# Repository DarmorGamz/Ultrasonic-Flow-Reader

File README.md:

<!-- PROJECT LOGO -->
<br />
<div align="center">
  
<h3 align="center">Ultrasonic Flow Reader</h3>

  <p align="center">
    The Ultra Sonic Flow Reader is a non-invasive, innovative solution that enables real-time water flow monitoring in pipes using ultrasonic waves. Designed for homeowners, residential and industrial building owners, and property managers, this device helps reduce installation costs and risks associated with traditional inline installations, while promoting water conservation and potential cost savings.
    <br />
    <br />
    <a href="https://github.com/DarmorGamz/Ultrasonic-Flow-Reader">View Demo</a>
    ·
    <a href="https://github.com/DarmorGamz/Ultrasonic-Flow-Reader/issues">Report Bug</a>
    ·
    <a href="https://github.com/DarmorGamz/Ultrasonic-Flow-Reader/issues">Request Feature</a>
  </p>
</div>

### Built With

[![C][C.com]][C-url]

[![HTML.com]][HTML-url] [![CSS3.com]][CSS3-url] [![JavaScript.com]][JavaScript-url]

[![PHP.com]][PHP-url] [![MYSQL.com]][MYSQL-url] [![Linux.com]][Linux-url] [![AWS.com]][AWS-url]

<!-- ABSTRACT -->
## ABSTRACT
The Ultra Sonic Flow Reader is a non-invasive solution designed to measure the flow of water in pipes using ultrasonic waves, eliminating the need for costly and time-consuming inline installation by licensed plumbers. Targeting homeowners, residential and industrial building owners, and property managers, this innovative device empowers users to monitor their water usage in real time, leading to potential cost savings and improved water conservation. The project employs ultrasonic transducers, a SAMD20 microcontroller, Winc1500 for WiFi, ENC28J60 for Ethernet, and leverages AWS for RDS, EC2, and Route53. The firmware is developed using Embedded C, with a PHP backend, and a frontend designed using HTML, CSS, and JavaScript. The Ultra Sonic Flow Reader is expected to minimize the need for hiring plumbers and reduce the risk of potential damage associated with traditional inline installations. The project's final demonstration is scheduled for April 13, 2023, showcasing a user-friendly and efficient solution for real-time water usage monitoring.

<!-- INTRODUCTION -->
## INTRODUCTION

#### Enhancing Water Usage Monitoring
The Ultra Sonic Flow Reader project was conceived with the primary goal of addressing a pressing need in the field of water monitoring and management. Traditional methods for measuring water flow in pipes typically require invasive installations and the assistance of licensed plumbers. This process can be both expensive and time-consuming, posing significant challenges for homeowners, residential and industrial building owners, and property managers who are looking to monitor their water usage in real time. As water scarcity becomes an increasingly critical global issue, there is a growing demand for innovative solutions that facilitate efficient water management and conservation.

#### Target Users and Applications
The project's scope encompasses the design and development of a non-invasive, cost-effective, and user-friendly device capable of real-time water usage monitoring. The Ultra Sonic Flow Reader employs advanced technologies such as ultrasonic transducers, a SAMD20 microcontroller, Winc1500 for WiFi, and ENC28J60 for Ethernet. In addition, it leverages Amazon Web Services (AWS) for database management (RDS), cloud computing (EC2), and domain name management (Route53). The device's firmware is developed using Embedded C, while the backend is built using PHP, and the frontend is designed with HTML, CSS, and JavaScript.

#### Project Development Phases
The approach taken to the project involved extensive research, planning, and execution of various design phases, including hardware and software development, integration, and testing. The interdisciplinary team, consisting of Darren Morrison, Austin Cormier, and Carter Glynn, collaborated closely under the supervision of Professors Hameed Al-Aubodah, Hamood-ur Rehman, Jane Carr, and Mehrdad Hajivandi to bring the project to fruition.

#### Challenges of Traditional Inline Installations
The Ultra Sonic Flow Reader project has been designed with a focus on simplicity, adaptability, and ease of use. Recognizing the diverse needs of homeowners, property managers, and residential and industrial building owners, the team has strived to create a solution that caters to a wide range of applications. The device's non-invasive nature ensures that it can be installed without causing disruptions to existing infrastructure or requiring specialized skills.
Throughout the project, the team has been guided by a set of core principles, including innovation, collaboration, and a commitment to addressing real-world challenges. These principles have driven the development process and informed key decisions, such as the selection of appropriate hardware components, software design, and integration strategies. Additionally, the team has placed a strong emphasis on testing and validation, ensuring that the Ultra Sonic Flow Reader consistently delivers accurate and reliable results.
As the project progresses towards its final demonstration, scheduled for April 13, 2023, the team remains dedicated to refining the Ultra Sonic Flow Reader and addressing any outstanding issues or limitations. The team acknowledges that further research and development efforts will be essential in enhancing the device's applicability to a wider range of pipe sizes and optimizing its power supply requirements. By addressing these challenges, the Ultra Sonic Flow Reader will be better positioned to meet the needs of its target users and make a positive impact on water management and conservation efforts.
In summary, the Ultra Sonic Flow Reader project represents a significant advancement in the field of water monitoring and management. By offering a non-invasive, cost-effective, and user-friendly solution for real-time water usage monitoring, the device has the potential to transform the way homeowners, building owners, and property managers approach water conservation. This report serves to document the project's journey from conception to completion, providing a comprehensive account of the team's research, development, and validation efforts.
This report details the problem statement, which outlines the challenges faced by traditional inline water flow monitoring systems and the need for a non-invasive alternative. The development process, including the project proposal, changes and decisions made throughout the project, and challenges encountered in implementation, is thoroughly discussed. Furthermore, the report presents the testing procedures and results, including Sprint tests, Product Validation tests, and an assessment of whether all user needs and requirements have been met. To support the report, relevant research materials, schematics, flowcharts, source code, and other documentation are included in the appendices.

#### Problem Statement
The Ultra Sonic Flow Reader project aims to revolutionize water monitoring by providing a solution that eliminates the need for hiring plumbers and reduces the risk of potential damage associated with traditional inline installations. By offering real-time water usage monitoring, the device empowers users to make informed decisions about their water consumption, leading to potential cost savings and improved water conservation efforts.

#### Report Structure
This report is organized into several sections, each focusing on a different aspect of the project. Following the introduction, the report details the problem statement, project development process, testing procedures and results, and any remaining limitations or challenges. The appendices provide additional documentation and materials to support the main body of the report.

<!-- INTRODUCTION -->
## DISCUSSION
The development of the Ultra Sonic Flow Reader project can be broken down into several key phases, each contributing to the overall success of the project. In this section, we discuss the progression of the project from proposal to completion, highlighting the changes and decisions made, challenges faced during implementation, and the various tests conducted.

#### Project Proposal and Initial Development
The project proposal was the foundation for the Ultra Sonic Flow Reader, outlining the primary objectives, expected outcomes, and proposed timeline. The team performed extensive research on existing flow measurement methods, identifying the limitations and drawbacks of traditional inline installations. This analysis informed the decision to pursue a non-invasive solution using ultrasonic waves for flow measurement.
Initial development focused on selecting appropriate hardware components, such as the ultrasonic transducers and SAMD20 microcontroller, and designing the basic hardware structure. The team also began work on the firmware using Embedded C and the backend using PHP, laying the groundwork for further development.

#### Iterative Development and Integration
Throughout the project, the team adopted an iterative development process, allowing for continuous improvements and adjustments. Hardware and software components were developed in parallel, with regular integration and testing to ensure compatibility and functionality.
Several changes were made during the development process, including the addition of Winc1500 for WiFi connectivity, ENC28J60 for Ethernet support, and the utilization of AWS for cloud-based services. These changes were made to enhance the device's usability and align it with modern IoT-based solutions.

#### Challenges and Implementation
The team encountered various challenges during the implementation phase. These included limited funding, time constraints, and complexities in debugging and hardware design. To overcome these challenges, the team members worked collaboratively, leveraging their individual skills and expertise to find solutions.
One of the key challenges was ensuring accurate flow measurement across various pipe sizes and materials. The team focused on refining the ultrasonic transducer placement and signal processing algorithms to achieve reliable results. Furthermore, optimizing power consumption was a priority, and the team worked on designing an energy-efficient system that minimizes the need for additional power sources.

#### Testing and Results
The Ultra Sonic Flow Reader underwent a series of tests to ensure its functionality, accuracy, and reliability. These tests included User Information Handling, API testing, Hardware Event Handling, and Hardware Timers testing. Each test was designed to evaluate specific aspects of the device's performance and identify areas for improvement.
The results of these tests showed that the Ultra Sonic Flow Reader met most user needs and requirements, delivering accurate flow measurements and a responsive user interface. However, some limitations were identified, such as the need for a more modular sensor PCB mount and optimization of the power supply.

#### References to Appendices
Throughout the report, references are made to the appendices, which contain supplementary material such as research materials, schematics, flowcharts, and source code. These documents provide a more in-depth understanding of the Ultra Sonic Flow Reader's design and development process and can be used to replicate the project and verify its results.

<!-- RECOMMENDATION -->
## RECOMMENDATION
Based on the findings and conclusions of the Ultra Sonic Flow Reader project, the following recommendations are provided to guide future research, development, and commercialization efforts.

#### Wider Pipe Size Compatibility
The current design supports only 1-inch pipes, limiting the applicability of the device. Future research should focus on developing a more modular sensor PCB mount, enabling compatibility with a broader range of pipe sizes to cater to various residential and industrial applications.

#### Power Supply Optimization
The power supply requirements of the current design demand a minimum of 12V for the sensor PCB to function. Optimizing the power supply to support lower voltage levels could enhance the device's energy efficiency, minimize the need for additional power sources, and potentially extend its battery life.

#### Enhanced User Interface
While the existing user interface is functional, it could benefit from further refinement to improve user experience. Future iterations should consider incorporating more advanced data visualization features, customizable alerts, and a mobile application for increased accessibility.

#### Market Research and Consumer Feedback
Conduct market research and solicit feedback from potential end-users to gain insights into user needs, preferences, and potential use cases. This information can inform future design decisions and contribute to the development of a more market-ready product.

#### Compliance with Regulatory Standards
As the project moves towards commercialization, it is crucial to research safety requirements, electronic stamping, and other relevant industry standards to ensure the Ultra Sonic Flow Reader complies with all necessary regulations.

#### Cost Reduction and Production Efficiency
To improve profit margins and streamline production, consider bulk purchasing of components, outsourcing board soldering, and adopting lean manufacturing practices.

#### Long-term Testing and Reliability
Further long-term testing should be conducted to assess the device's durability, performance consistency, and overall reliability under various environmental conditions and extended usage periods.
By addressing these recommendations, the Ultra Sonic Flow Reader can evolve into a more refined and market-ready product, better positioned to meet the needs of its target users and contribute significantly to water conservation efforts.

<!-- APPENDICES -->
## APPENDICES
#### Schematics

Fig. 1.	MCU - Atmel SAMD20 circuit.

Fig. 2.	Wifi – Winc1500 circuit.

Fig. 3.	Ethernet – ENC28J60 circuit.

Fig. 4.	Sensor – Ultra sonic flow reader circuit.   

#### Flowcharts

Fig. 5. Cloud – AWS design flowchart

<!-- GETTING STARTED -->
## Getting Started

This is an example of how you may give instructions on setting up your project locally.
To get a local copy up and running follow these simple example steps.

### Prerequisites

### Installation

<p align="right">(<a href="#readme-top">back to top</a>)</p>

<!-- CONTRIBUTING -->
## Contributing

Contributions are what make the open source community such an amazing place to learn, inspire, and create. Any contributions you make are **greatly appreciated**.

If you have a suggestion that would make this better, please fork the repo and create a pull request. You can also simply open an issue with the tag "enhancement".
Don't forget to give the project a star! Thanks again!

1. Fork the Project
2. Create your Feature Branch (`git checkout -b feature/AmazingFeature`)
3. Commit your Changes (`git commit -m 'Add some AmazingFeature'`)
4. Push to the Branch (`git push origin feature/AmazingFeature`)
5. Open a Pull Request

<p align="right">(<a href="#readme-top">back to top</a>)</p>

<!-- LICENSE -->
## License

Distributed under the Eyedro Green Solutions License. See `LICENSE.txt` for more information.

<p align="right">(<a href="#readme-top">back to top</a>)</p>

<!-- CONTACT -->
## Contact

Darren Morrison - darren09@live.ca  
Austin Cormier - austin14cormier@gmail.com   
Carter Glynn - carter.glynn14@gmail.com  

Project Link: [https://github.com/DarmorGamz/Ultrasonic-Flow-Reader](https://github.com/DarmorGamz/Ultrasonic-Flow-Reader)

<p align="right">(<a href="#readme-top">back to top</a>)</p>

<!-- ACKNOWLEDGMENTS -->
## Acknowledgments
We are deeply grateful to the following individuals for their invaluable contributions, guidance, and support during the development of the Ultra Sonic Flow Reader project:   

#### Dr. Hameed Al-Aubodah, PhD
*For his expertise in electrical theory (DC, AC, Transmission lines) and digital design, and for being an inspiring role model in the engineering field.*

#### Dr. Hamood-Ur Rehman, PhD
*For sharing essential software and programming knowledge, ensuring elegant, readable, and maintainable code, and for setting high expectations that contributed to the project's success.*

#### Dr. Mehrdad Hajivandi, PhD P.Eng
*For his guidance in mathematics and advanced thinking principles crucial to the project's development.*

#### Jane Carr
*For her expertise in testing, debugging, verification, and documentation, which played a significant role in the project's completion.*   
<br />
We also extend our appreciation to Eyedro Green Solutions for their generous funding, access to lab equipment, and invaluable mentorship throughout the project. Special thanks to:   

#### Trevor Orton, CEO
*For his guidance in cloud computing, backend development, and writing and maintaining quality code.*

#### Nick Gamble, CFO
*For sharing his expertise in embedded software, embedded systems, networking, and data analysis.*

#### Jeff Conley
*For his dedication to hardware design, product specifications, circuit design, PCB assembly, and document review.*  

<p align="right">(<a href="#readme-top">back to top</a>)</p>

<!-- REFERENCES -->
## References

T. Dean, "Sonar," Brown University, [Online]. Available: https://cs.brown.edu/people/tdean/courses/cs148/02/sonar.html.  
D. Russell, "The Doppler Effect," Kettering University, [Online]. Available: https://web.archive.org/web/20071119085900/http://www.kettering.edu/~drussell/Demos/doppler/doppler.html.  
University of Bristol, "Time-of-Flight Mass Spectrometry," [Online]. Available: https://web.archive.org/web/20120310184539/http://www.chm.bris.ac.uk/ms/theory/tof-massspec.html.  
J. Steensgaard, "Bootstrapped low-voltage analog switches," in 1999 IEEE International Symposium on Circuits and Systems (ISCAS), Orlando, FL, USA, 1999, pp. 29-32, vol.2, doi: 10.1109/ISCAS.1999.780611.  
Microchip Technology Inc., "SAMD20 Family Datasheet," [Online]. Available: https://ww1.microchip.com/downloads/en/DeviceDoc/SAM_D20_Family_Datasheet_DS60001504C.pdf.  
Microchip Technology Inc., "ENC28J60 Stand-Alone Ethernet Controller with SPI Interface," [Online]. Available: https://ww1.microchip.com/downloads/aemDocuments/documents/OTH/ProductDocuments/DataSheets/39662e.pdf. 
Microchip Technology Inc., "ATWINC15x0-MR210xB IEEE 802.11 b/g/n SmartConnect IoT Module," [Online]. Available: https://ww1.microchip.com/downloads/aemDocuments/documents/WSG/ProductDocuments/DataSheets/ATWINC15x0-MR210xB-IEEE-802.11-b-g-n-SmartConnect-IoT-Module-DS70005304E.pdf.  
Amazon Web Services, "Amazon EC2 User Guide," [Online]. Available: https://docs.aws.amazon.com/AWSEC2/latest/UserGuide/concepts.html.  
Amazon Web Services, "Amazon RDS User Guide," [Online]. Available: https://docs.aws.amazon.com/AmazonRDS/latest/UserGuide/Welcome.html.  

<p align="right">(<a href="#readme-top">back to top</a>)</p>

<!-- MARKDOWN LINKS & IMAGES -->
<!-- https://www.markdownguide.org/basic-syntax/#reference-style-links -->
[contributors-shield]: https://img.shields.io/github/contributors/DarmorGamz/Ultrasonic-Flow-Reader.svg?style=for-the-badge
[contributors-url]: https://github.com/DarmorGamz/Ultrasonic-Flow-Reader/graphs/contributors
[forks-shield]: https://img.shields.io/github/forks/DarmorGamz/Ultrasonic-Flow-Reader.svg?style=for-the-badge
[forks-url]: https://github.com/DarmorGamz/Ultrasonic-Flow-Reader/network/members
[stars-shield]: https://img.shields.io/github/stars/DarmorGamz/Ultrasonic-Flow-Reader.svg?style=for-the-badge
[stars-url]: https://github.com/DarmorGamz/Ultrasonic-Flow-Reader/stargazers
[issues-shield]: https://img.shields.io/github/issues/DarmorGamz/Ultrasonic-Flow-Reader.svg?style=for-the-badge
[issues-url]: https://github.com/DarmorGamz/Ultrasonic-Flow-Reader/issues
[license-shield]: https://img.shields.io/github/license/DarmorGamz/Ultrasonic-Flow-Reader.svg?style=for-the-badge
[license-url]: https://github.com/DarmorGamz/Ultrasonic-Flow-Reader/blob/master/LICENSE.txt
[linkedin-shield]: https://img.shields.io/badge/-LinkedIn-black.svg?style=for-the-badge&logo=linkedin&colorB=555
[linkedin-url]: https://linkedin.com/in/darren--morrison

[C.com]: https://img.shields.io/badge/c-%2300599C.svg?style=for-the-badge&logo=c&logoColor=white
[C-url]: https://www.cprogramming.com
[PHP.com]: https://img.shields.io/badge/php-%23777BB4.svg?style=for-the-badge&logo=php&logoColor=white
[PHP-url]: https://www.php.net/
[MYSQL.com]: https://img.shields.io/badge/mysql-%2300f.svg?style=for-the-badge&logo=mysql&logoColor=white
[MYSQL-url]: https://www.mysql.com/
[HTML.com]: https://img.shields.io/badge/html5-%23E34F26.svg?style=for-the-badge&logo=html5&logoColor=white
[HTML-url]: https://www.w3.org/html/#:~:text=W3C%20HTML&text=https%3A%2F%2Fhtml.spec.whatwg,is%20the%20current%20HTML%20standard.
[CSS3.com]: https://img.shields.io/badge/css3-%231572B6.svg?style=for-the-badge&logo=css3&logoColor=white
[CSS3-url]: https://www.css3.com/
[JavaScript.com]: https://img.shields.io/badge/javascript-%23323330.svg?style=for-the-badge&logo=javascript&logoColor=%23F7DF1E
[JavaScript-url]: https://www.javascript.com/

[Linux.com]: https://img.shields.io/badge/Linux-FCC624?style=for-the-badge&logo=linux&logoColor=black
[Linux-url]: https://aws.amazon.com/amazon-linux-2/

[AWS.com]: https://img.shields.io/badge/AWS-%23FF9900.svg?style=for-the-badge&logo=amazon-aws&logoColor=white
[AWS-url]: https://aws.amazon.com/

[PHPStorm.com]: https://img.shields.io/badge/phpstorm-143?style=for-the-badge&logo=phpstorm&logoColor=black&color=black&labelColor=darkorchid
[PHPStorm-url]: https://www.jetbrains.com/phpstorm/

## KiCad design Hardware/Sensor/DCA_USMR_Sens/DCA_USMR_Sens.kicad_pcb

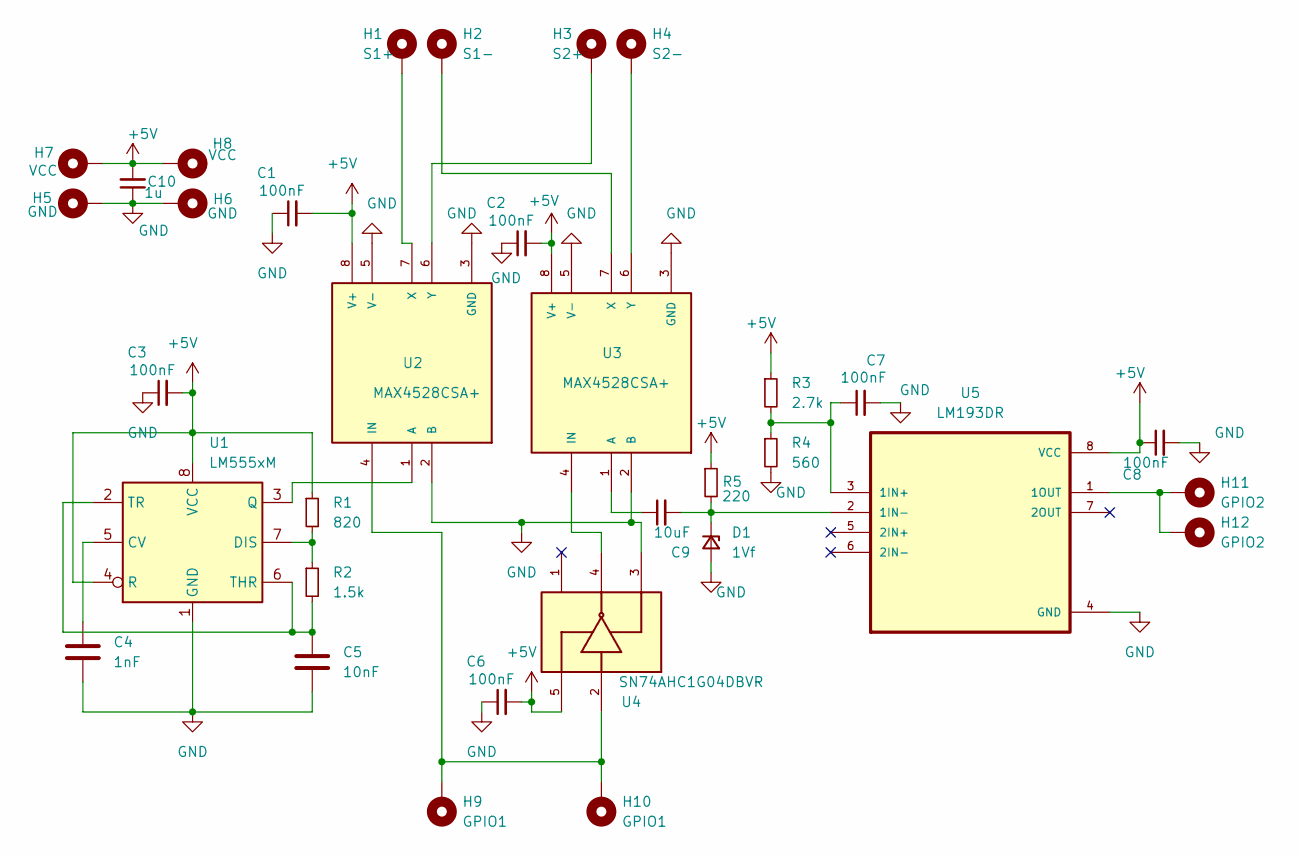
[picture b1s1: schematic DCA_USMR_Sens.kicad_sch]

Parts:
C1, C2, C3, C6, C7, C8: 100nF; C_0402_1005Metric
C4: 1nF; C_0402_1005Metric
C5: 10nF; C_0402_1005Metric
C9: 10uF; C_0402_1005Metric
C10: 1u; C_0603_1608Metric
D1: 1Vf; DIOAD835W50L444D203
H1: S1+; Pin_D0.7mm_L6.5mm_W1.8mm_FlatFork
H2: S1-; Pin_D0.7mm_L6.5mm_W1.8mm_FlatFork
H3: S2+; Pin_D0.7mm_L6.5mm_W1.8mm_FlatFork
H4: S2-; Pin_D0.7mm_L6.5mm_W1.8mm_FlatFork
H5, H6: GND; Pin_D0.7mm_L6.5mm_W1.8mm_FlatFork
H7, H8: VCC; Pin_D0.7mm_L6.5mm_W1.8mm_FlatFork
H9, H10: GPIO1; Pin_D0.7mm_L6.5mm_W1.8mm_FlatFork
H11, H12: GPIO2; Pin_D0.7mm_L6.5mm_W1.8mm_FlatFork
R1: 820; R_0402_1005Metric
R2: 1.5k; R_0402_1005Metric
R3: 2.7k; R_0402_1005Metric
R4: 560; R_0402_1005Metric
R5: 220; R_0402_1005Metric
U1: LM555xM; SOIC-8_3.9x4.9mm_P1.27mm
U2, U3: MAX4528CSA+; SOIC127P600X175-8N
U4: SN74AHC1G04DBVR; SOT95P280X145-5N; PARTREV AD
U5: LM193DR; SOIC127P599X175-8N

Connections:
+5V: C1.2, C2.2, C3.2, C6.2, C8.1, C10.2, H7.1, H8.1, R1.1, R3.1, R5.1, U1.4 (R), U1.8 (VCC), U2.8 (V+), U3.8 (V+), U4.5, U5.8 (VCC)
GND: C1.1, C2.1, C3.1, C4.2, C5.2, C6.1, C7.2, C8.2, C10.1, D1.2 (A), H5.1, H6.1, R4.2, U1.1 (GND), U2.2 (B), U2.3 (GND), U2.5 (V-), U3.2 (B), U3.3 (GND), U3.5 (V-), U4.3, U5.4 (GND)
unnamed: C4.1, U1.5 (CV)
unnamed: C5.1, R2.2, U1.2 (TR), U1.6 (THR)
unnamed: C7.1, R3.2, R4.1, U5.3 (1IN+)
unnamed: C9.1, U3.1 (A)
unnamed: C9.2, D1.1 (K), R5.2, U5.2 (1IN-)
unnamed: R1.2, R2.1, U1.7 (DIS)
unnamed: U1.3 (Q), U2.1 (A)
unnamed: H9.1, H10.1, U2.4 (IN), U4.2
unnamed: H3.1, U2.6 (Y)
unnamed: H1.1, U2.7 (X)
unnamed: U3.4 (IN), U4.4
unnamed: H4.1, U3.6 (Y)
unnamed: H2.1, U3.7 (X)
unnamed: H11.1, H12.1, U5.1 (1OUT)

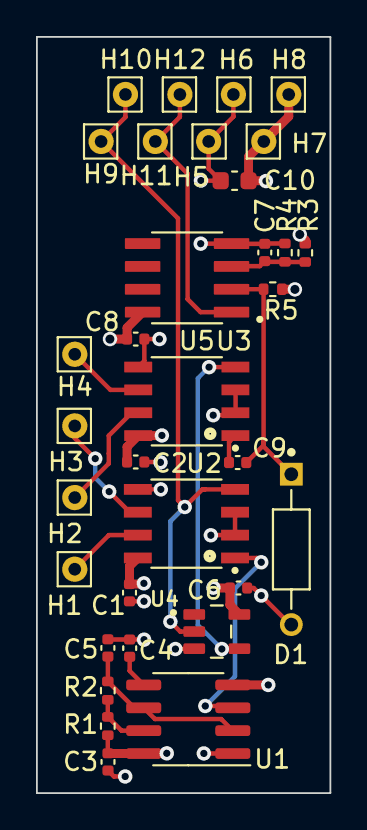
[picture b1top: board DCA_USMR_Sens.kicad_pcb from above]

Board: 4 copper layers, 16.3 x 42.0 mm, 33 parts (0 on the bottom side), 16 nets.

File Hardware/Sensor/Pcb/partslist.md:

# PARTS LIST

### IC's

**(1x)** Comparator - LM193DR <br>
https://www.digikey.ca/en/products/detail/texas-instruments/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 <br>

**(2x)** Switch - MAX4528CSA+ <br>
https://www.digikey.ca/en/products/detail/analog-devices-inc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 <br>

**(1x)** 555 Timer - LM555CMMX/NOPB  <br>
https://www.digikey.ca/en/products/detail/texas-instruments/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 <br>

**(1x)** Inverter - SN74AHC1G04DBVR <br>
https://www.digikey.ca/en/products/detail/texas-instruments/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 <br>

### CAPACITORS

**(1x)** 1uF <br>
**(6x)** 100nF <br>
**(2x)** 10nF <br>
**(1x)** 1nF <br>

### RESISTORS

**(1x)** 220Ω <br>
**(1x)** 560Ω <br>
**(1x)** 820Ω <br>
**(1x)** 1.5kΩ <br>
**(1x)** 2.7kΩ <br>

### DIODE

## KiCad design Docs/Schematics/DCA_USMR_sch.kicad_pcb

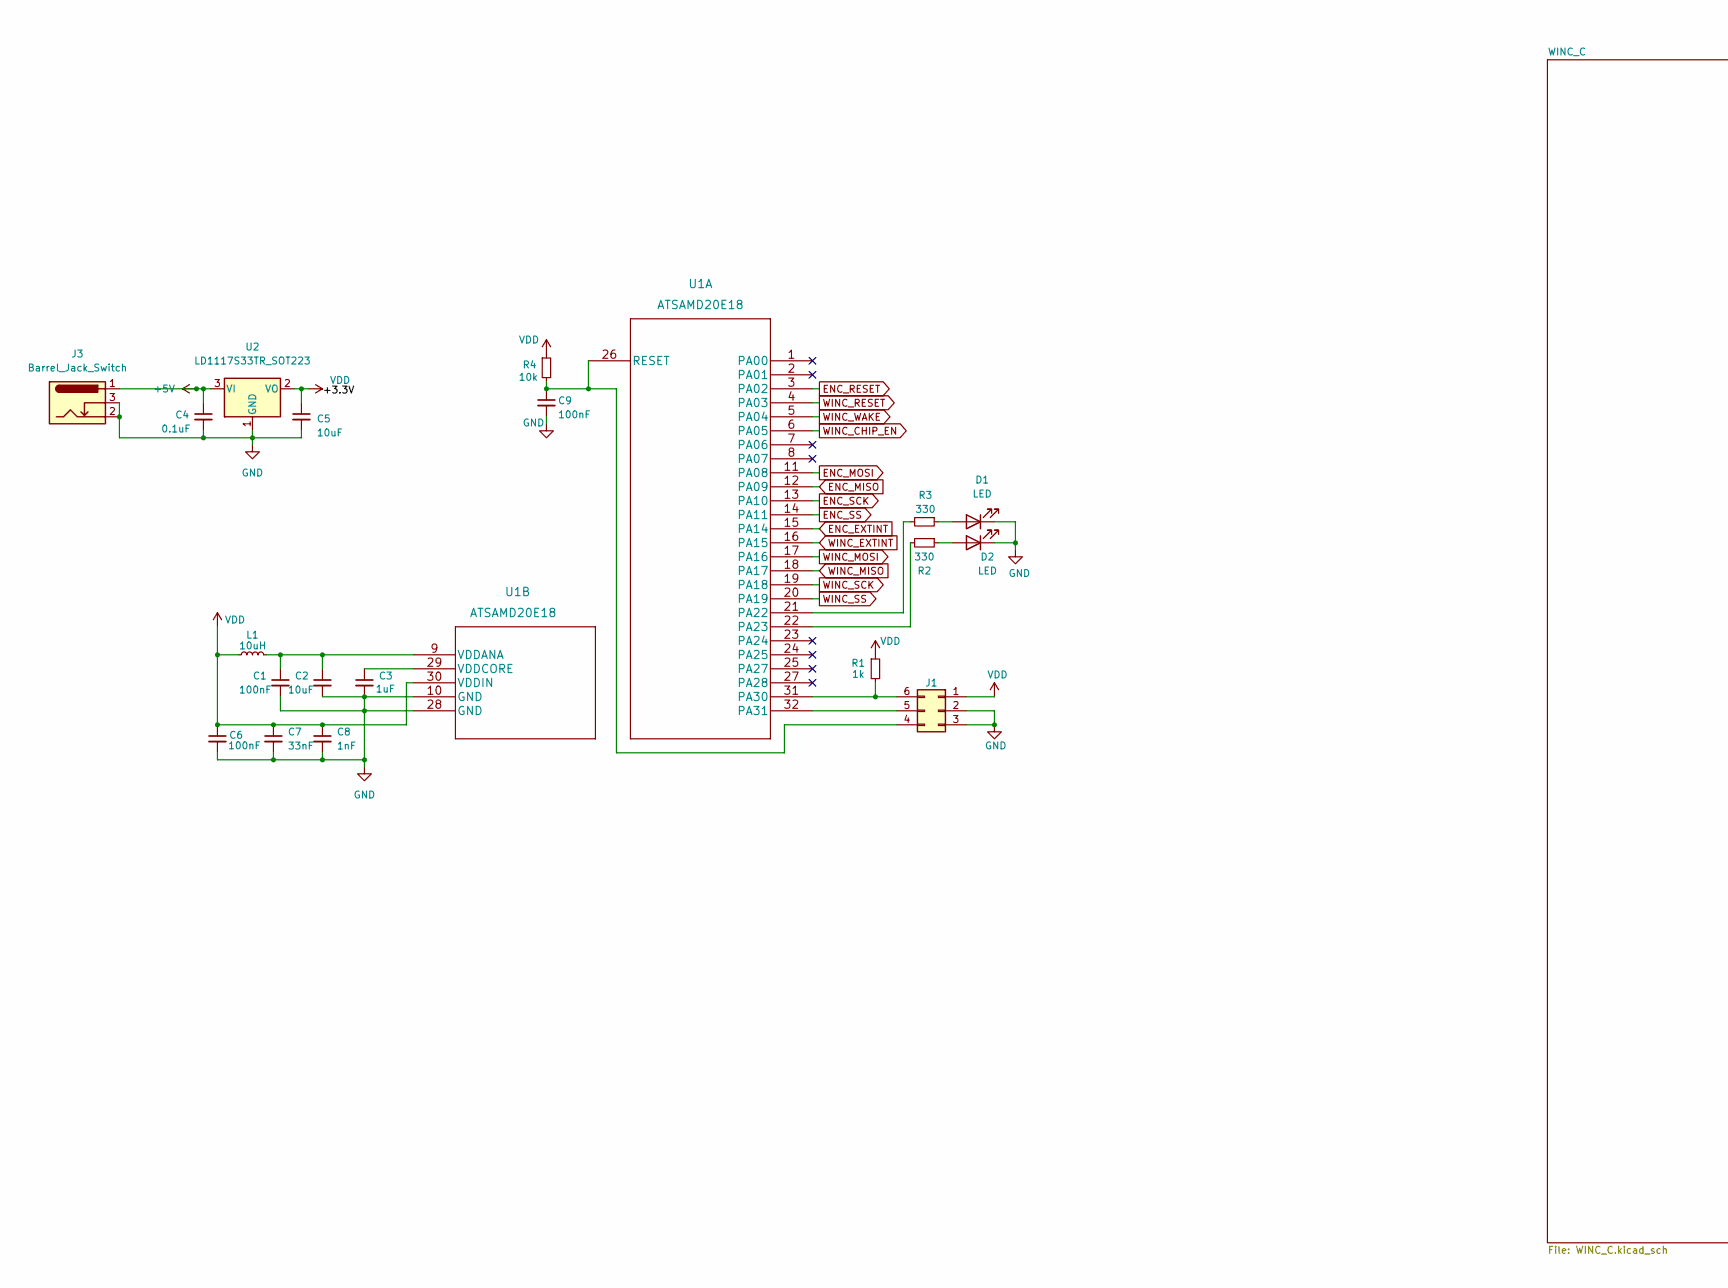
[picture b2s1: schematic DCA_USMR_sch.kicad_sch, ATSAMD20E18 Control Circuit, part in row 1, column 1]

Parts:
C1, C6, C9: 100nF; C_0402_1005Metric
C2, C5: 10uF; C_0402_1005Metric
C3: 1uF; C_0402_1005Metric
C4: 0.1uF; C_0402_1005Metric
C7: 33nF; C_0402_1005Metric
C8: 1nF; C_0402_1005Metric
D1, D2: LED; LED_0402_1005Metric
J1: Conn_02x03_Counter_Clockwise; PinHeader_2x03_P2.00mm_Vertical
J3: Barrel_Jack_Switch; CUI_PJ-018H-SMT-TR
L1: 10uH; L_0603_1608Metric
R1: 1k; R_0402_1005Metric
R2, R3: 330; R_0402_1005Metric
R4: 10k; R_0402_1005Metric
U1: ATSAMD20E18; ATSAMD20E18A-AU
U2: LD1117S33TR_SOT223; SOT-223-3_TabPin2

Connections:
+5V: C4.1, J3.1, J3.1A, U2.3 (VI)
ENC_EXTINT: U1.15 (PA14); also elsewhere on the board
ENC_MISO: U1.12 (PA09); also elsewhere on the board
ENC_MOSI: U1.11 (PA08); also elsewhere on the board
ENC_RESET: U1.3 (PA02); also elsewhere on the board
ENC_SCK: U1.13 (PA10); also elsewhere on the board
ENC_SS: U1.14 (PA11); also elsewhere on the board
GND: C1.2, C2.2, C3.2, C4.2, C5.2, C6.2, C7.2, C8.2, C9.2, D1.1 (K), D2.1 (K), J1.2, J1.3, J3.2, J3.3, U1.10 (GND), U1.28 (GND), U2.1 (GND); also elsewhere on the board
unnamed: C1.1, C2.1, L1.2, U1.9 (VDDANA)
unnamed: C3.1, U1.29 (VDDCORE)
unnamed: C9.1, J1.4, R4.2, U1.26 (RESET)
unnamed: D1.2 (A), R3.1
unnamed: D2.2 (A), R2.1
unnamed: J1.5, U1.32 (PA31)
unnamed: J1.6, R1.2, U1.31 (PA30)
unnamed: R2.2, U1.22 (PA23)
unnamed: R3.2, U1.21 (PA22)
VDD: C5.1, C6.1, C7.1, C8.1, J1.1, L1.1, R1.1, R4.1, U1.30 (VDDIN), U2.2 (VO); also elsewhere on the board
WINC_CHIP_EN: U1.6 (PA05); also elsewhere on the board
WINC_EXTINT: U1.16 (PA15); also elsewhere on the board
WINC_MISO: U1.18 (PA17); also elsewhere on the board
WINC_MOSI: U1.17 (PA16); also elsewhere on the board
WINC_RESET: U1.4 (PA03); also elsewhere on the board
WINC_SCK: U1.19 (PA18); also elsewhere on the board
WINC_SS: U1.20 (PA19); also elsewhere on the board
WINC_WAKE: U1.5 (PA04); also elsewhere on the board

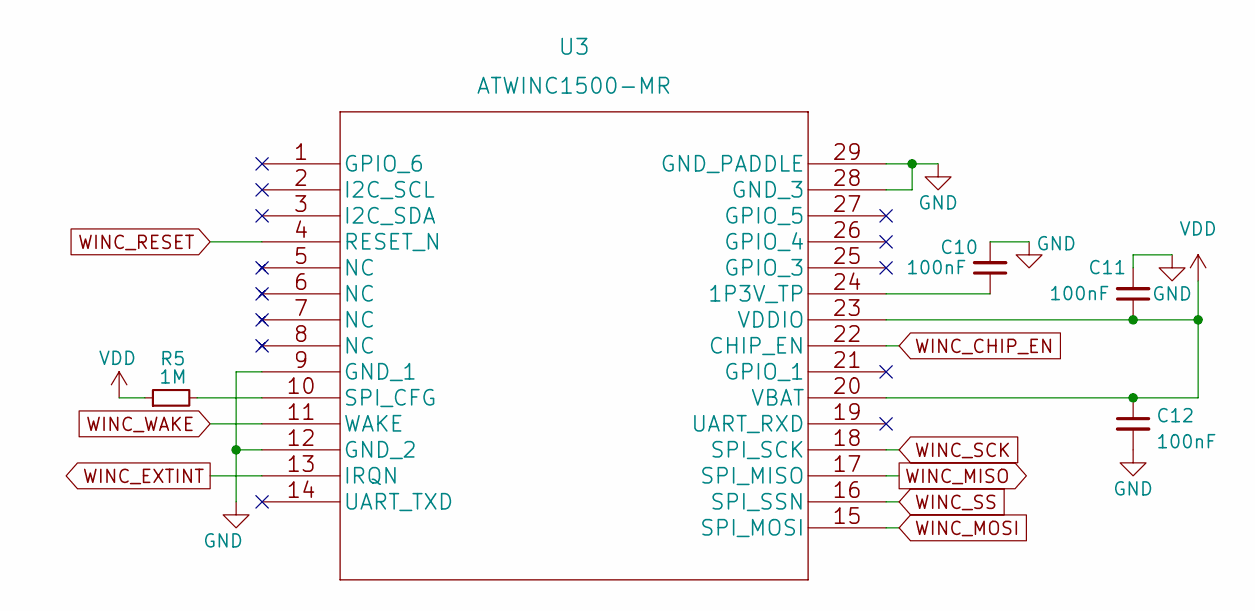
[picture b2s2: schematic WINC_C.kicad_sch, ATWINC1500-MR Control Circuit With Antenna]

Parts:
C10, C11, C12: 100nF; C_0402_1005Metric
R5: 1M; R_0402_1005Metric
U3: ATWINC1500-MR; ATWINC1500-MR210PB1961

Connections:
GND: C10.2, C11.2, C12.2, U3.9 (GND_1), U3.12 (GND_2), U3.28 (GND_3), U3.29 (GND_PADDLE); also elsewhere on the board
unnamed: C10.1, U3.24 (1P3V_TP)
unnamed: R5.2, U3.10 (SPI_CFG)
VDD: C11.1, C12.1, R5.1, U3.20 (VBAT), U3.23 (VDDIO); also elsewhere on the board
WINC_CHIP_EN: U3.22 (CHIP_EN); also elsewhere on the board
WINC_EXTINT: U3.13 (IRQN); also elsewhere on the board
WINC_MISO: U3.17 (SPI_MISO); also elsewhere on the board
WINC_MOSI: U3.15 (SPI_MOSI); also elsewhere on the board
WINC_RESET: U3.4 (RESET_N); also elsewhere on the board
WINC_SCK: U3.18 (SPI_SCK); also elsewhere on the board
WINC_SS: U3.16 (SPI_SSN); also elsewhere on the board
WINC_WAKE: U3.11 (WAKE); also elsewhere on the board

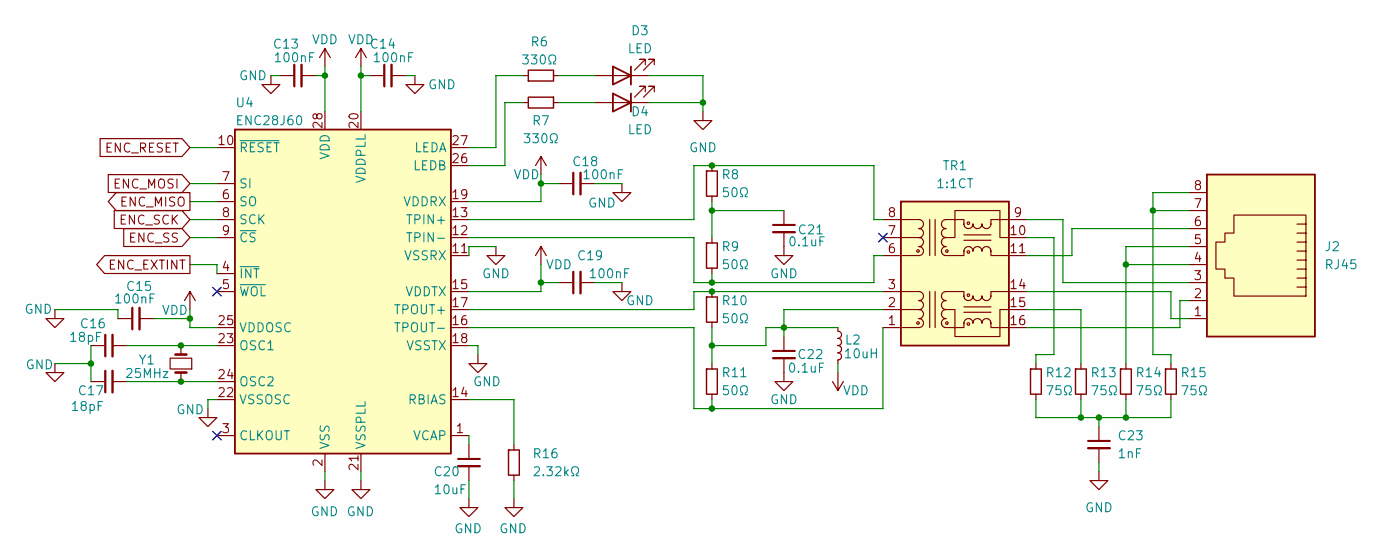
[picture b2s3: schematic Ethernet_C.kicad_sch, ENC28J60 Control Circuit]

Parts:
C13, C14, C15, C18, C19: 100nF; C_0402_1005Metric
C16, C17: 18pF; C_0402_1005Metric
C20: 10uF; C_0402_1005Metric
C21, C22: 0.1uF; C_0402_1005Metric
C23: 1nF; C_0402_1005Metric
D3, D4: LED; LED_0402_1005Metric
J2: RJ45; RJ45_Plug_Metz_AJP92A8813
L2: 10uH; L_0603_1608Metric
R6, R7: 330Ω; R_0402_1005Metric
R8, R9, R10, R11: 50Ω; R_0402_1005Metric
R12, R13, R14, R15: 75Ω; R_0402_1005Metric
R16: 2.32kΩ; R_0402_1005Metric
TR1: 1:1CT; Transformer_Ethernet_Bourns_PT61017PEL
U4: ENC28J60; SSOP-28_5.3x10.2mm_P0.65mm
Y1: 25MHz; XTAL_ECS-160-20-4X

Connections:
ENC_EXTINT: U4.4 (~INT); also elsewhere on the board
ENC_MISO: U4.6 (SO); also elsewhere on the board
ENC_MOSI: U4.7 (SI); also elsewhere on the board
ENC_RESET: U4.10 (~RESET); also elsewhere on the board
ENC_SCK: U4.8 (SCK); also elsewhere on the board
ENC_SS: U4.9 (~CS); also elsewhere on the board
GND: C13.1, C14.2, C15.1, C16.1, C17.1, C18.2, C19.2, C20.2, C21.2, C22.2, C23.2, D3.1 (K), D4.1 (K), R16.2, U4.2 (VSS), U4.11 (VSSRX), U4.18 (VSSTX), U4.21 (VSSPLL), U4.22 (VSSOSC); also elsewhere on the board
unnamed: C16.2, U4.23 (OSC1), Y1.2
unnamed: C17.2, U4.24 (OSC2), Y1.1
unnamed: C20.1, U4.1 (VCAP)
unnamed: C21.1, R8.2, R9.1
unnamed: C22.1, L2.1, R10.2, R11.1, TR1.2 (C_TD)
unnamed: C23.1, R12.2, R13.2, R14.2, R15.2
unnamed: D3.2 (A), R6.2
unnamed: D4.2 (A), R7.1
unnamed: J2.1, TR1.14 (TX-)
unnamed: J2.2, TR1.16 (TX+)
unnamed: J2.3, TR1.9 (RX-)
unnamed: J2.4, J2.5, R14.1
unnamed: J2.6, TR1.11 (RX+)
unnamed: J2.7, J2.8, R15.1
unnamed: R6.1, U4.27 (LEDA)
unnamed: R7.2, U4.26 (LEDB)
unnamed: R8.1, TR1.8 (RD-), U4.13 (TPIN+)
unnamed: R9.2, TR1.6 (RD+), U4.12 (TPIN-)
unnamed: R10.1, TR1.3 (TD-), U4.17 (TPOUT+)
unnamed: R11.2, TR1.1 (TD+), U4.16 (TPOUT-)
unnamed: R12.1, TR1.10 (C_RX)
unnamed: R13.1, TR1.15 (C_TX)
unnamed: R16.1, U4.14 (RBIAS)
VDD: C13.2, C14.1, C15.2, C18.1, C19.1, L2.2, U4.15 (VDDTX), U4.19 (VDDRX), U4.20 (VDDPLL), U4.25 (VDDOSC), U4.28 (VDD); also elsewhere on the board

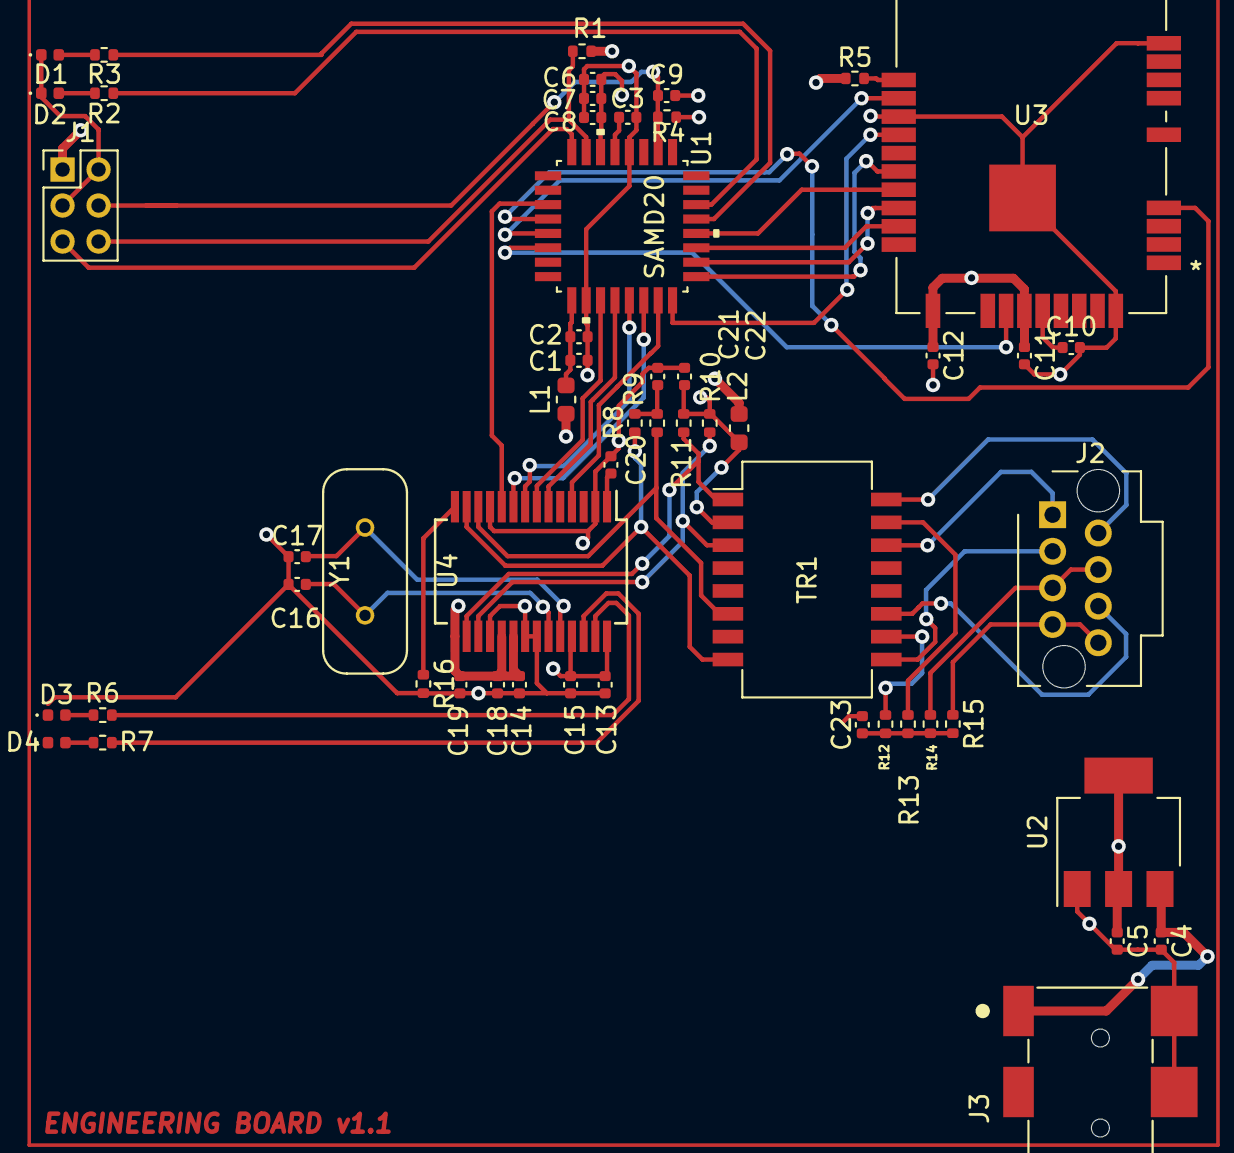
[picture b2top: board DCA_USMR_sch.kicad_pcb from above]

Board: 4 copper layers, 54 parts (0 on the bottom side), 51 nets.

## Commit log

2022-09-28 Add files via upload
    SAMD21 Dev board guide
    SAMD21 WINC with Dev board guide.
2022-10-24 Add files via upload
    Provision page for winc1500. Must update winc1500 firmware to send to flash memory
2022-10-29 Refactor repository.
2022-11-01 Revision 2
    Fixes based after sponsor interview.
2022-11-03 Revision 3
    Revisions made after meeting with sponsor.
2022-11-03 Revision 1
    Block Diagram Revision 1
2022-11-03 Add files via upload
    Weekly Report for sprint 2 week 1
2022-11-04 Firmware flowchart v1.0
2022-11-09 Reformated Firmware structure Built from Atmel Start
    All GPIO pins declared
    Added Watchdog
    Added Timer
    Added Wifi
    Added Ethernet
    Added Main App Program Loop
2022-11-10 Weekly Report 221110
2022-11-10 PCB_Revision_1
    Before sponsor changes
2022-11-10 Revision 4
    Merged into 1 sheet after meeting with sponsor
2022-11-10 PCB Captures v1.0
2022-11-10 Schematic PDF
2022-11-12 Revision v1.1
    Main PCB changes, Moved power to bottom right. Made power rails 0.5mil.
2022-11-16 Updated Repo organization. Board Schematic, Pcb, and Gerbers all updated. First set of Engineering boards ordered on 221115
2022-11-17 Sprint 2 Week 4 Report
    PCB ordered, sensor module completed
2022-11-18 First version of Flow Sensor module
2022-11-18 Firmware latest
2022-11-18 Fixed schematic issue. Inverter was going to input instead of control.
2022-12-08 Block Diagram for Sensor
2023-01-26 Create Project
2023-01-26 Updated weekly report template for week 11
2023-02-02 Sensor Rev1.1
    Rev1.1
2023-02-03 Revision 2
    v2.0.1
2023-02-06 Cleanup directory location
2023-02-06 First build of backend server. Amazon Linux 2.
2023-02-06 Newest version. Dns, Socket, and TCP state machines. Can connect to hw.darmorgamz.ca and send/recieve data.
2023-02-06 Newest board spin. Fixed Wifi, and ethernet SPI ports. Added Sensor connectors with digital In/Outs
2023-02-07 Sensor Updates. Boards Ordered.
2023-02-16 added images + small color changes
2023-02-16 graph and about basic layout, index basic styling
2023-02-22 might've had the wrong 555 in there whoops
2023-03-08 Frontend of Server facelift.
2023-03-09 Create Enclosure
2023-03-17 Repo cleanup
2023-03-17 Current Server version
2023-03-17 Current client version
2023-03-17 Useless af
2023-03-17 Current Backend Version
2023-03-17 Current Firmware version
2023-03-23 Latest Server version
2023-03-23 Login no longer re-casted to 'User.Get'. Has it's own block functionality. Password changed to PwdMd5. Hashed when it comes in, and is stored as PwdMd5 in DB. ResetPassword Cmd now exists. Requires E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
2023-03-23 Added Functionality to Reset Password button. Apache on the server removed redirect. You must access /index2.php to see client. / is used for Hw root because im lazy. Data on backend is now limited t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
2023-03-23 Looks pretty. Idk.
2023-03-23 User.Del functionality added.
2023-03-23 User Delete funcationality added in Configuration. Email/Username was only appearing on NavBar for Demand page. Now appears on all pages. Signed-off-by: Darren <Darmor>
2023-03-30 highchart homepage works
2023-03-30 redirects working again lol
2023-03-30 Reading buffer with rolling 1sec average using 32bit tick timer. two buffers are used, one will be reading, one with me writing.
2023-03-30 First point in averaging algo isn't a time difference, it's the current ticks. This causes the first data point to be higher than expected.
2023-03-30 Test report for Hardware events
2023-03-30 Tests for Hardware Timers
2023-04-12 Images created for Final Report
2023-04-12 Changes made for Sensor EXT. Sensor comparator is so fast that the main program loop get blocked. Collects 128 Avg points per second and then turns off EXT. EXT turned back on every 1sec callback.
2023-04-12 Final report
2023-04-12 added .gitignore for firmware and backend directories
2023-04-12 Removed phpMyAdmin from Backend directory.
2023-04-12 Moved images and documents to correct directory.
2023-04-12 Moved to correct directory.
2023-04-12 Un needed example project
2023-04-12 un needed.
2023-04-12 Un needed directory.
2023-04-12 Moved reports to it's own subdirectory
2023-04-12 Moved documents to their own directory.
2023-04-12 Documents in correct directory.
2023-04-12 Moved to docs directory
2023-04-12 Moved to documents directory
2023-04-12 Removed .gitignored files from cache
2023-04-12 Firmware backup projects
2023-04-12 Added contact GSAD. Removed un needed data.get
2023-04-12 Directory Rename
2023-04-12 Removed file. Not nedded.
2023-04-12 Added contact page. Form submits requests to database.
2023-04-12 Made login page nav, match rest of website.
2023-04-12 Added sticky Nav bar.
2023-04-12 Added sticky Nav bar. Updated Awesome font version.
2023-04-12 Update clock functionality is not needed.
2023-04-12 Updated nav bar to be sticky and dynamic
2023-04-12 Made hamburger menu dynamic
2023-04-12 Create about page for project.
2023-04-12 Temp removal of highcharts. Need to get data correctly.
2023-04-12 Renamed logo. Added svgs for about page.
2023-04-12 rick roll
2023-04-12 Added sticky nav bar. Updated Awesome fonts version

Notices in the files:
parts and their libraries:
Copyright 2021 Accelerated Designs. All rights reserved.
